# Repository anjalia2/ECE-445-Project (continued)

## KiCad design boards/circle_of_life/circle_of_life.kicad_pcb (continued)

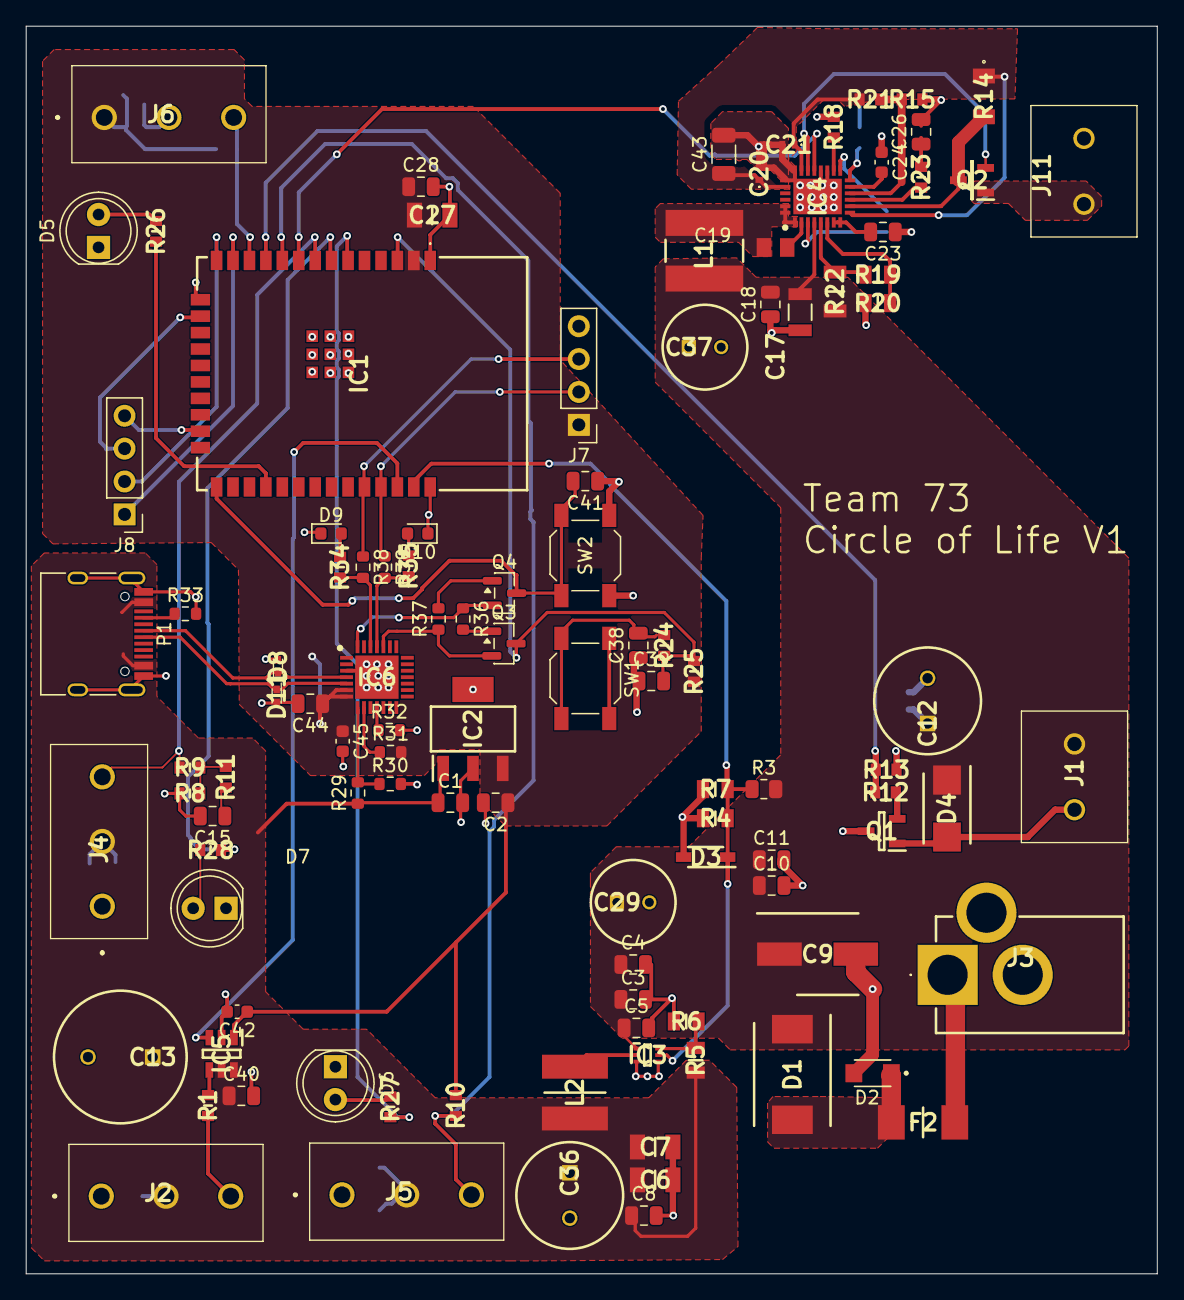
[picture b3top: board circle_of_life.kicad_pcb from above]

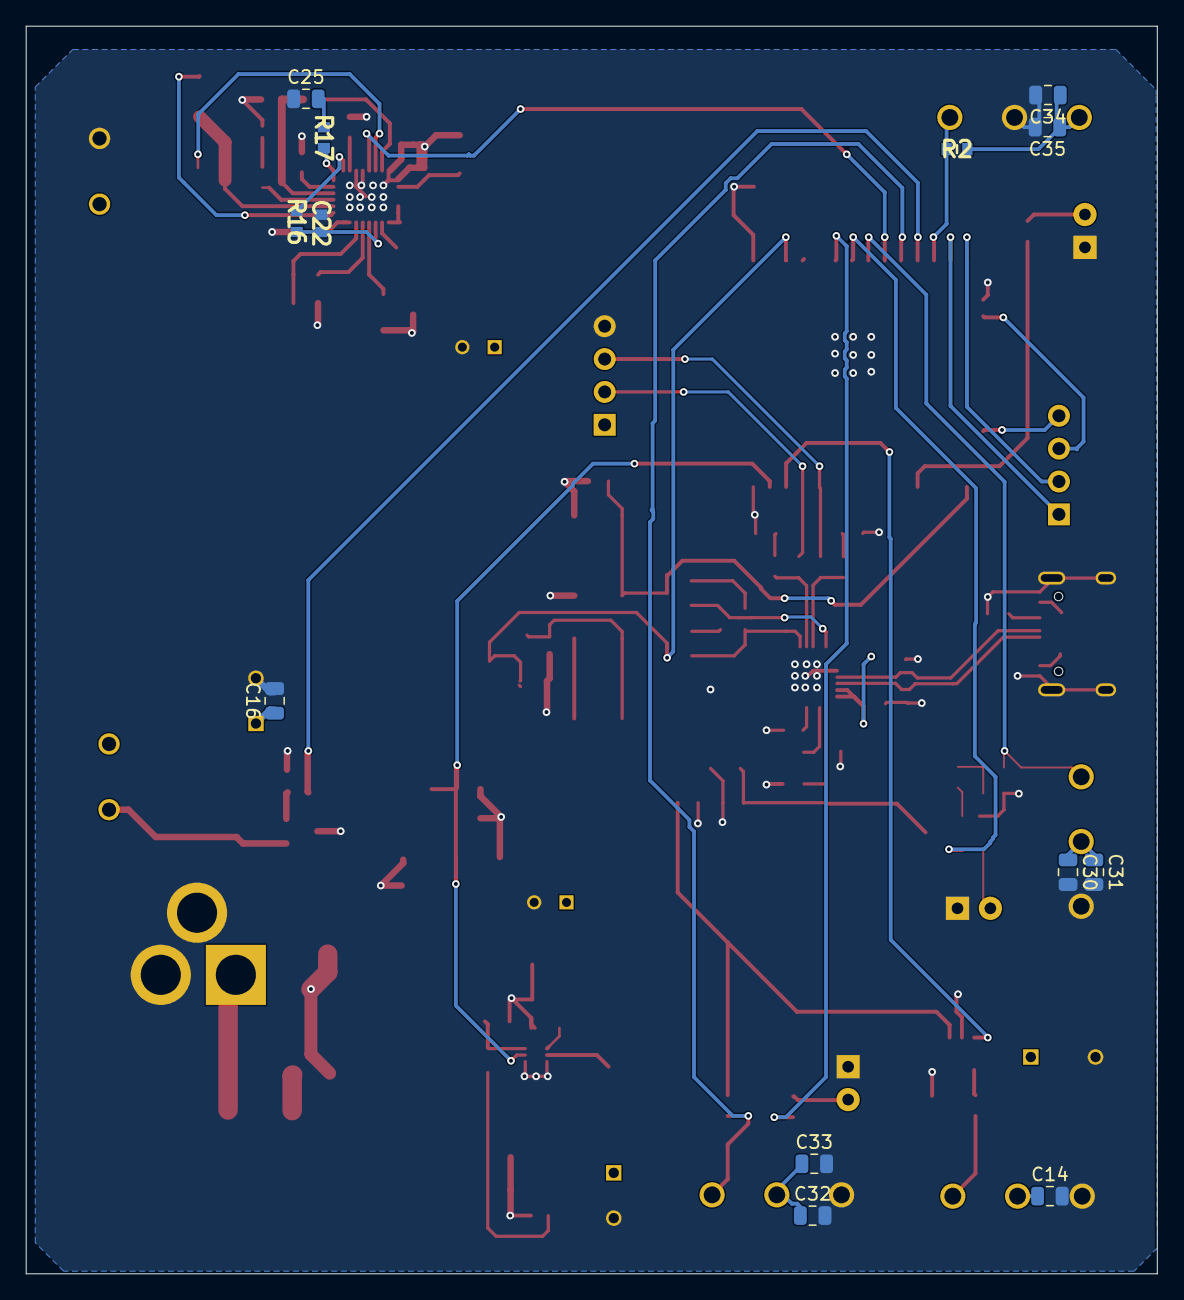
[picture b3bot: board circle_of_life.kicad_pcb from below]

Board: 2 copper layers, 87.4 x 96.4 mm, 120 parts (13 on the bottom side), 68 nets.

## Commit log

2026-02-10 Initial setup
2026-02-10 More repository setup
2026-02-18 Add README for Aishwarya Manoj Notebook
2026-02-19 Finalized first draft of schematic, missing inductor value for LED driver, rechecking all values, and adding footprints
2026-02-19 started assigning footprints
2026-02-19 more footprint assignments
2026-02-20 finished 74 out of 101 footprints
2026-02-20 most resistor footprints added, need to check
2026-02-20 Added level shifter to servo motor, and initiated layout, no routing yet
2026-02-20 slightly modified it
2026-02-21 added usb-uart programmer so that its easier to program :D
2026-02-23 5V signal routing done
2026-02-23 mcu connections started
2026-02-23 modified layout rip
2026-02-23 modified current sensor cause i just couldnt leave it like that
2026-02-24 started grow lights PCB
2026-02-24 updated grow lights board with wider traces & removed power plane
2026-02-24 made LED- the back copper
2026-02-25 fixed some footprints
2026-02-26 fixed most of the footprints errors
2026-02-26 Fixed DRC for main board
2026-02-26 finished generating files and put them in files folder for each PCB, also have zipped them
2026-02-27 modified some wrong values in led driver
2026-02-27 changed value
2026-03-01 Aishwarya's notebook updates
2026-03-01 Update README with project progress and plans
    Added new entries and updated project details in the README.
2026-03-01 notebook update aishwarya
2026-03-01 Revise README with project updates and details
    Updated the README.md to include detailed project notes and progress for the Aquaponics project.
2026-03-01 Update README with project details and progress
2026-03-01 Revise README for Aishwarya Manoj Notebook
    Updated README with project details and progress.
2026-03-01 Rename Screenshot 2026-03-01 165308.png to Screenshot2026-03-01165308.png
2026-03-01 Revise README with project updates and details
    Updated the README.md to include recent project updates and details about the Aquaponics project.
2026-03-05 Finished draft of second order PCB
2026-03-08 Added PCB V2
2026-03-09 Added code to folder
2026-03-09 with commentd & fixed pH print logic
2026-03-12 grow lights PCB
2026-03-26 code and grow lights pcb updates
2026-03-26 Updated grow lights board
2026-03-27 Routes fixed and resistors added
2026-04-10 temp sensor code
2026-04-16 pump code
2026-04-21 added led code
2026-04-23 dimming code v1
2026-04-23 new LED driver code to test
2026-04-25 more changes
2026-04-26 changed prints & offsets
2026-04-29 final code
2026-05-07 Uploaded Estela notebook
2026-05-07 Aishwarya's notebook updates committed
2026-05-07 Testing images
2026-05-07 Testing spacing
2026-05-07 Again
2026-05-07 Added sources
2026-05-07 Committing images to notebook for formatting
2026-05-07 Fixing formatting
2026-05-07 Fixing formatting again
2026-05-07 Fixing the image formatting again
2026-05-07 Fixing image formatting one last time
2026-05-07 Anjali's Lab Notebook
